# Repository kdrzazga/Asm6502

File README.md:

# Asm6502

HelloSprite - written in CBM prg Studio

HelloScroll - in KickAssembler

Sideborders - in KickAssembler

UserPort - ?

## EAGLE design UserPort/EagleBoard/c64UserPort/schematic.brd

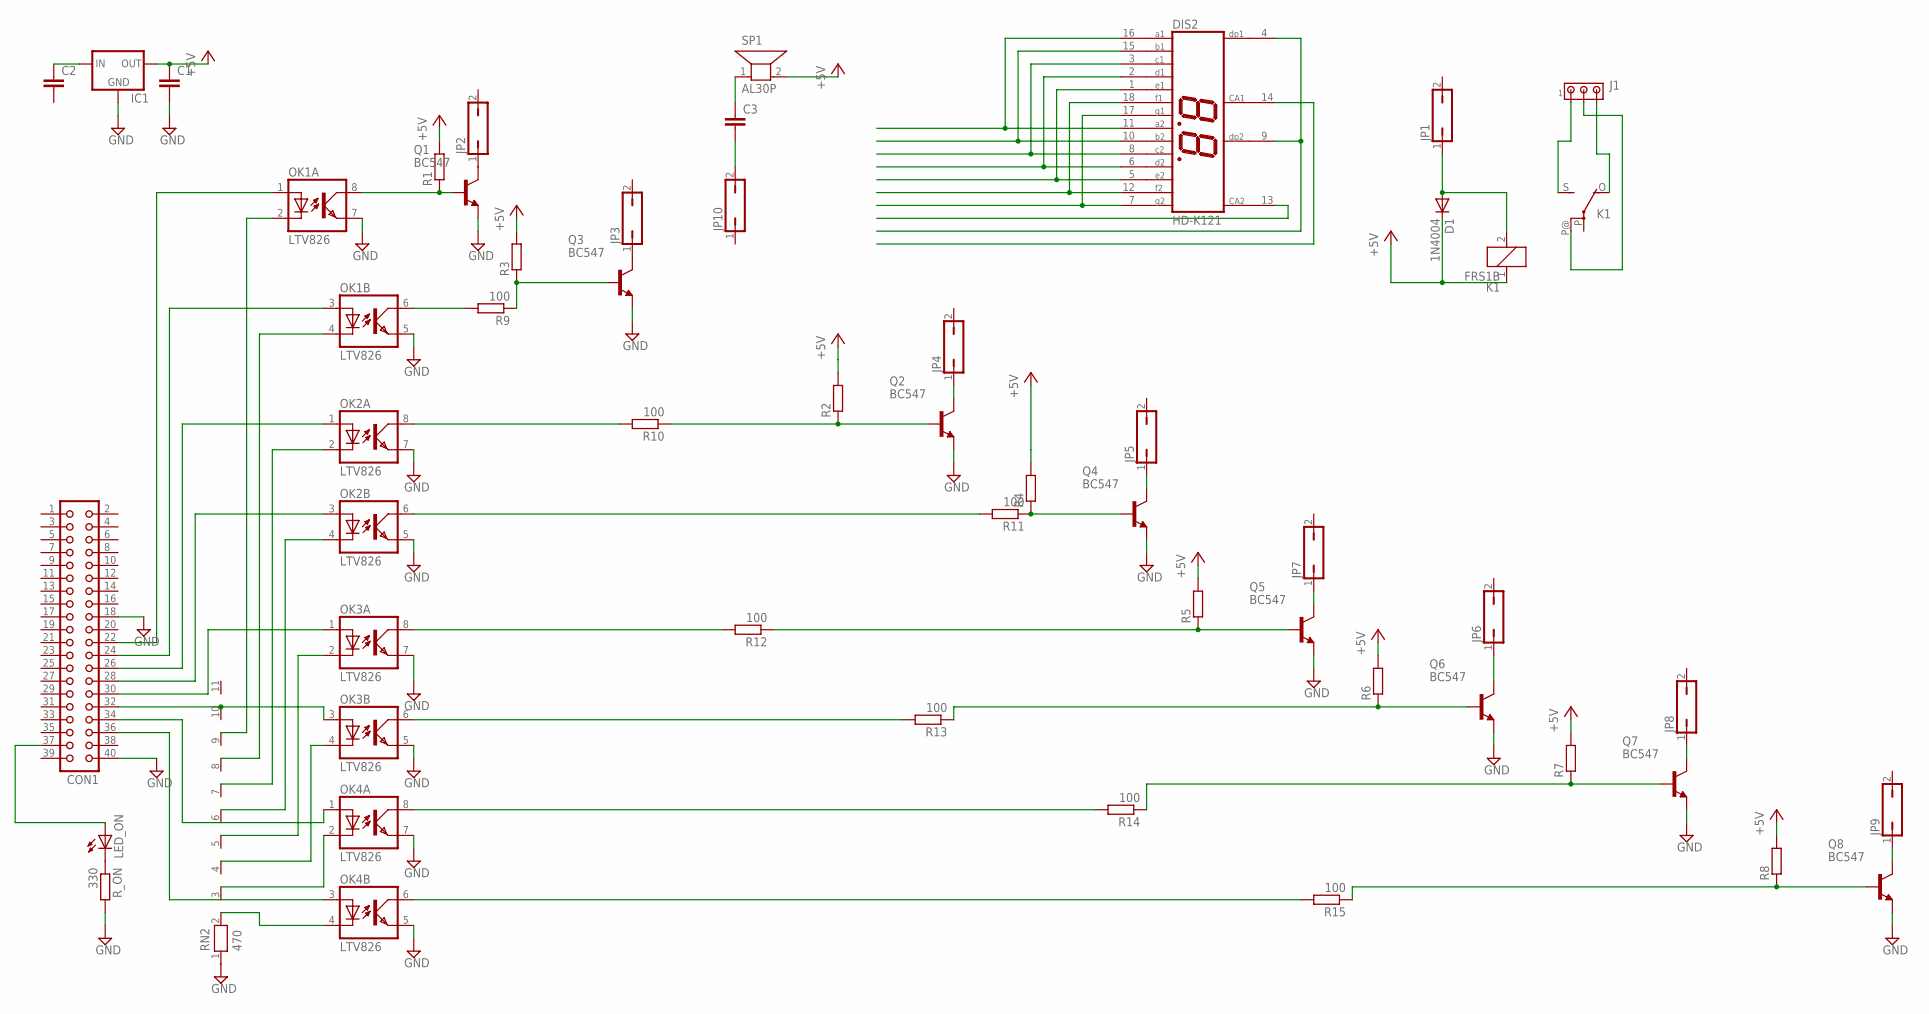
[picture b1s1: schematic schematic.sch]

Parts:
C1: C5/2.5; C5B2.5
C2, C3: C-EU075-063X106; C075-063X106
CON1: CON40
D1: 1N4004; DO41-10
DIS2: HD-K121; HDSP-R
IC1: 78MXXS
J1: MTA03-100; 10X03MTA
JP1, JP2, JP3, JP4, JP5, JP6, JP7, JP8, JP9, JP10: JP1Q; JP1
K1: FRS1B
LED_ON: LED3MM
OK1, OK2, OK3, OK4: LTV826; DIL08
Q1, Q2, Q3, Q4, Q5, Q6, Q7, Q8: BC547; TO92
R1, R2, R3, R4, R5, R6, R7, R8: R-EU_R3225; R3225
R9, R10, R11, R12, R13, R14, R15: 100; R3225
RN2: 470; RN-11
R_ON: 330; R3225
SP1: AL30P

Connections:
+5V: C1.1, D1.C, IC1.OUT, K1.1, R1.2, R3.2, R5.2, R6.2, R7.2, R8.2, SP1.2
GND: C1.2, CON1.18, CON1.40, IC1.GND, OK1.5 (EMIT), OK1.7 (EMIT), OK2.5 (EMIT), OK2.7 (EMIT), OK3.5 (EMIT), OK3.7 (EMIT), OK4.5 (EMIT), OK4.7 (EMIT), Q1.1 (E), Q2.1 (E), Q3.1 (E), Q4.1 (E), Q5.1 (E), Q6.1 (E), Q7.1 (E), Q8.1 (E), RN2.1, R_ON.2
unnamed: OK4.4 (C), RN2.2
unnamed: OK4.2 (C), RN2.3
unnamed: OK3.4 (C), RN2.4
unnamed: OK3.2 (C), RN2.5
unnamed: OK2.4 (C), RN2.6
unnamed: OK2.2 (C), RN2.7
unnamed: OK1.4 (C), RN2.8
unnamed: OK1.2 (C), RN2.9
unnamed: Q2.2 (B), R2.1, R10.1
unnamed: Q3.2 (B), R3.1, R9.1
unnamed: OK1.8 (COL), Q1.2 (B), R1.1
unnamed: JP2.1, Q1.3 (C)
unnamed: D1.A, JP1.1, K1.2
unnamed: Q4.2 (B), R4.1, R11.1
unnamed: Q5.2 (B), R5.1, R12.1
unnamed: JP3.1, Q3.3 (C)
unnamed: Q6.2 (B), R6.1, R13.1
unnamed: JP4.1, Q2.3 (C)
unnamed: Q7.2 (B), R7.1, R14.1
unnamed: JP5.1, Q4.3 (C)
unnamed: Q8.2 (B), R8.1, R15.1
unnamed: JP6.1, Q6.3 (C)
unnamed: J1.2, K1.P@
unnamed: J1.1, K1.S
unnamed: J1.3, K1.O
unnamed: OK1.6 (COL), R9.2
unnamed: OK2.8 (COL), R10.2
unnamed: OK2.6 (COL), R11.2
unnamed: OK3.8 (COL), R12.2
unnamed: OK3.6 (COL), R13.2
unnamed: OK4.8 (COL), R14.2
unnamed: OK4.6 (COL), R15.2
unnamed: DIS2.11 (A2), DIS2.16 (A1)
unnamed: DIS2.10 (B2), DIS2.15 (B1)
unnamed: DIS2.3 (C1), DIS2.8 (C2)
unnamed: DIS2.2 (D1), DIS2.6 (D2)
unnamed: DIS2.1 (E1), DIS2.5 (E2)
unnamed: DIS2.12 (F2), DIS2.18 (F1)
unnamed: DIS2.7 (G2), DIS2.17 (G1)
unnamed: CON1.36, OK4.3 (A)
unnamed: CON1.34, OK4.1 (A)
unnamed: CON1.32, OK3.3 (A), RN2.10
unnamed: CON1.30, OK3.1 (A)
unnamed: CON1.28, OK2.3 (A)
unnamed: CON1.26, OK2.1 (A)
unnamed: CON1.22, OK1.1 (A)
unnamed: CON1.24, OK1.3 (A)
unnamed: CON1.37, LED_ON.A
unnamed: LED_ON.K (C), R_ON.1
unnamed: JP7.1, Q5.3 (C)
unnamed: JP9.1, Q8.3 (C)
unnamed: JP8.1, Q7.3 (C)
unnamed: C2.1, IC1.IN
unnamed: C3.2, JP10.2
unnamed: C3.1, SP1.1
unnamed: DIS2.4 (DP1), DIS2.9 (DP2)

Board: 2 copper layers, 50 parts (16 on the bottom side), 58 nets, no tracks yet.

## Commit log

2017-05-19 First code
2017-05-19 Moving hellosprite.asm
2017-05-20 Split to several files. Attempt to introduce more joystick contorols (movement) - so far not successful
2017-05-22 Splitting some files added tests for joystick library
2017-05-22 added low charset to code (included in basic runner), this help in tests
2017-05-23 (no comment)
2017-05-29 Add 2 files
2017-05-29 Polishing...
2019-03-30 Simple scroll
2019-03-30 Simple music
2019-05-19 Added PCB design
